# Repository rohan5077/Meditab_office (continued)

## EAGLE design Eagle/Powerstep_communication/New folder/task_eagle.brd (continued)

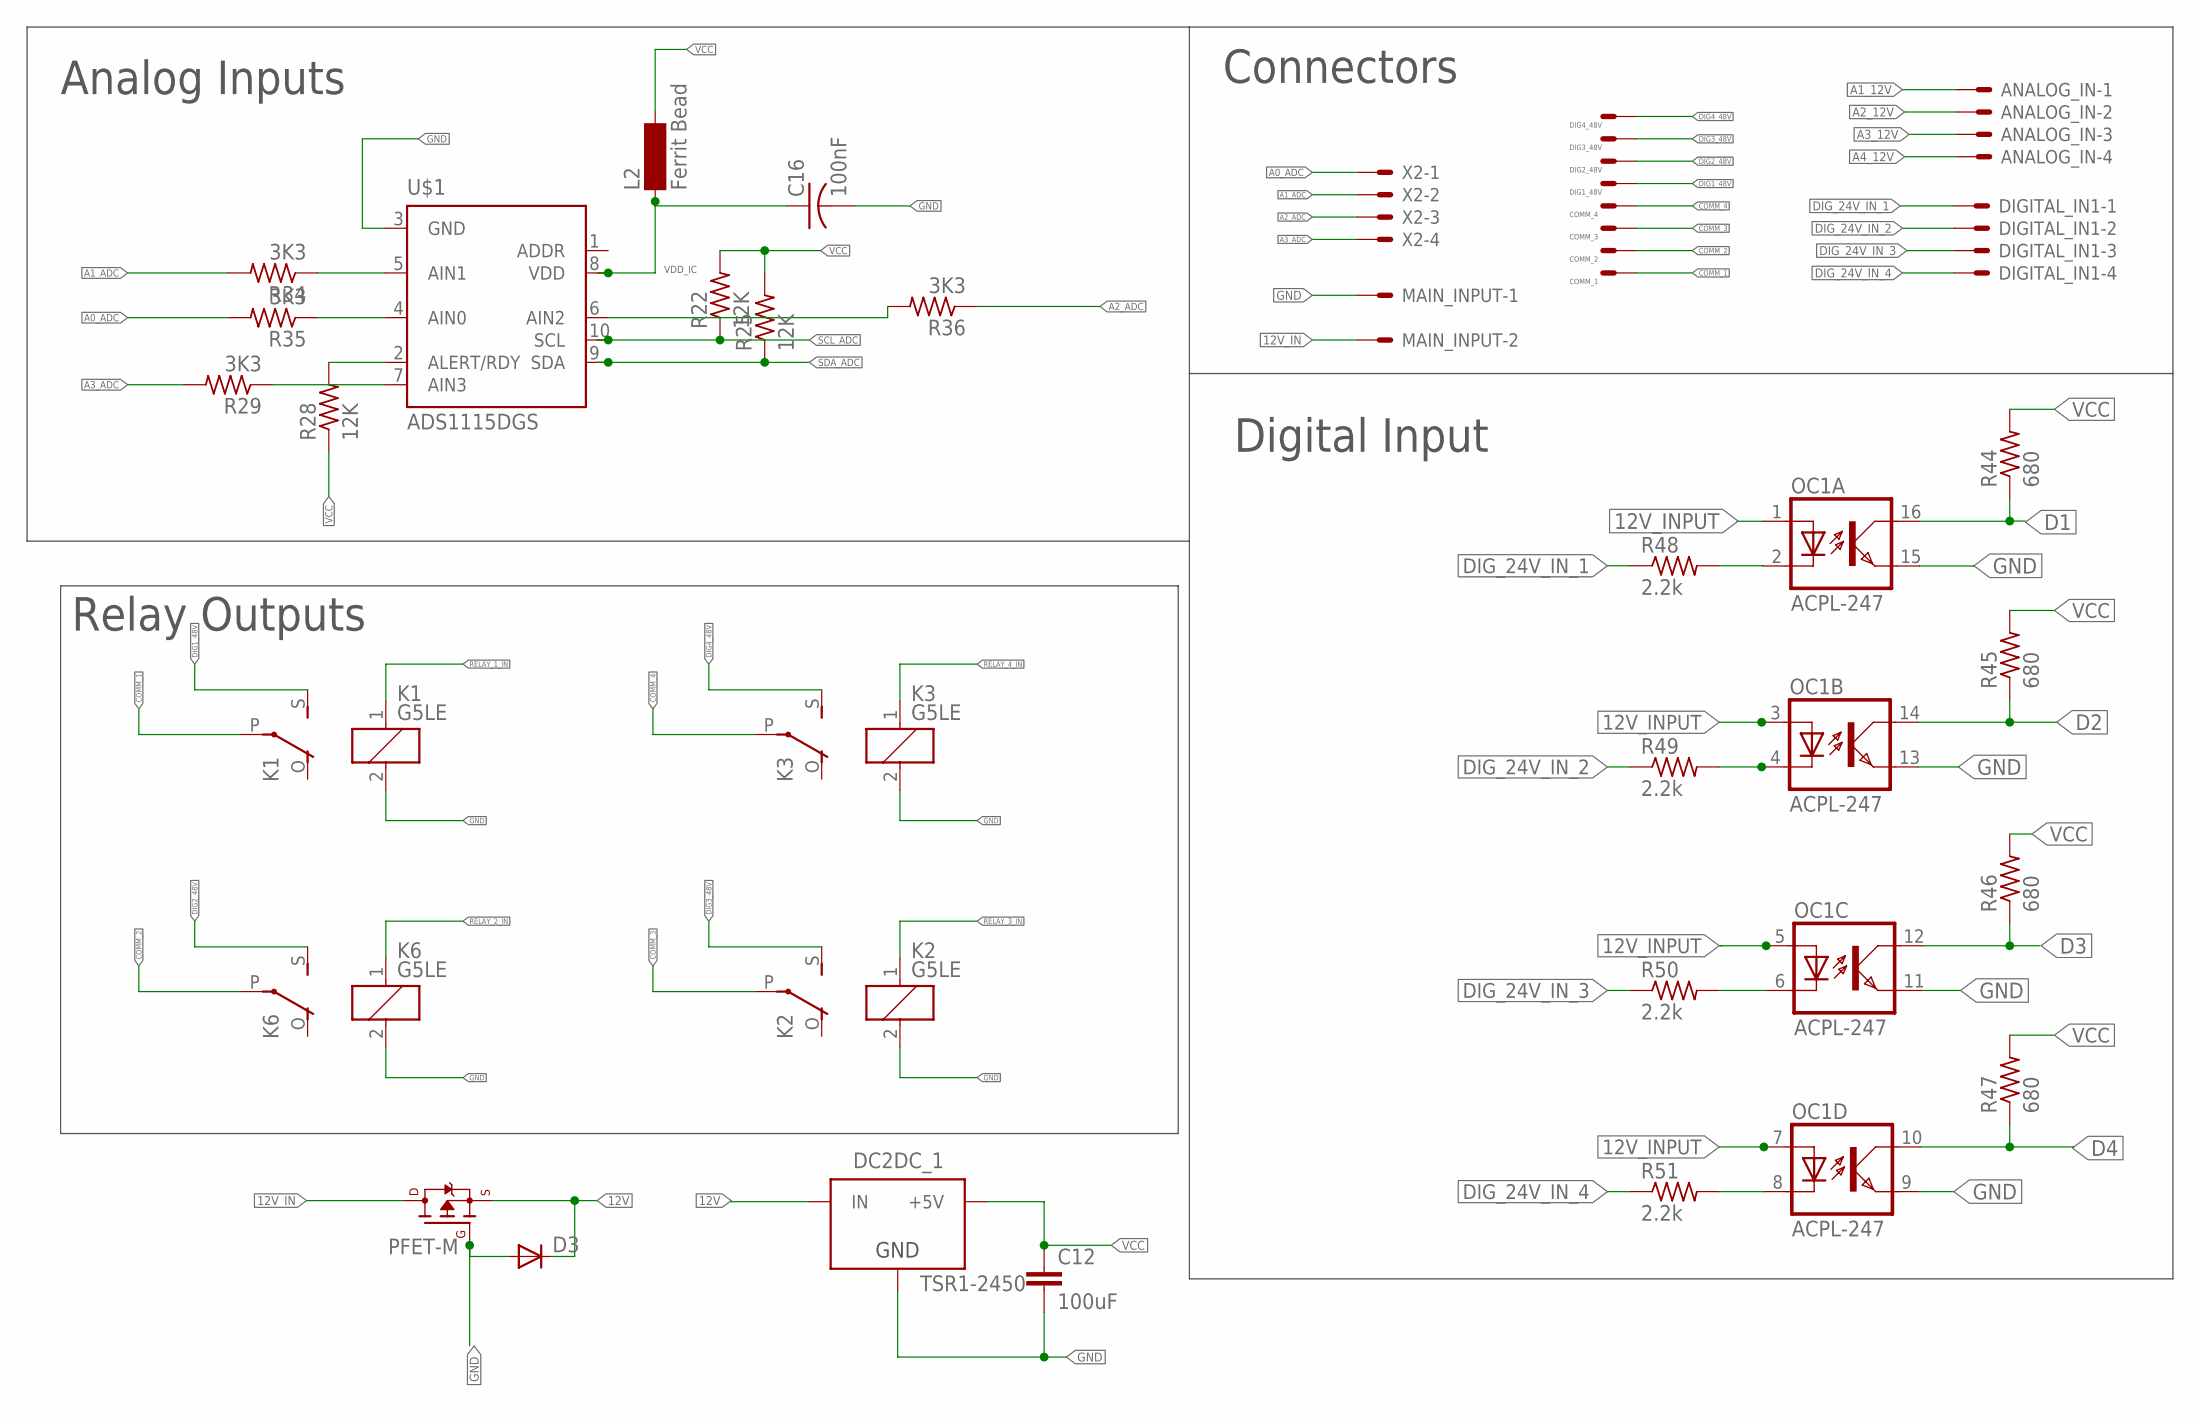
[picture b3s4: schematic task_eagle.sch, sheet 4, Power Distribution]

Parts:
ANALOG_IN: KK-156-4
C12: 100uF; C0603
C16: 100nF; C0603
D3: DIODE-MINIMELF; MINIMELF
DC2DC_1: TSR1-2450; TSR-1
DIGITAL_IN1: KK-156-4
K1, K2, K3, K6: G5LE
L2: Ferrit Bead; SM-1206
MAIN_INPUT: KK-156-2
OC1: ACPL-247; SOP16
PFET-M: FQP47P06NORMAL; FQP47P06-NORMAL
R22, R25, R28: 12K; R0603
R29, R34, R35, R36: 3K3; R0603
R44, R45, R46, R47: 680; R0603
R48, R49, R50, R51: 2.2k; R0603
U$1: ADS1115DGS; MSOP10
X2: KK-156-4
X3: KK-156-8

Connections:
12V: D3.C, DC2DC_1.1 (IN), PFET-M.3 (S)
12V_IN: MAIN_INPUT.2, PFET-M.2 (D)
12V_INPUT: OC1.1 (A), OC1.3 (A), OC1.5 (A), OC1.7 (A)
A0_ADC: R35.2, X2.1; also elsewhere on the board
A1_ADC: R34.2, X2.2; also elsewhere on the board
A2_ADC: R36.1, X2.3; also elsewhere on the board
A3_ADC: R29.2, X2.4; also elsewhere on the board
COMM_1: K1.P, X3.1
COMM_2: K6.P, X3.2
COMM_3: K2.P, X3.3
COMM_4: K3.P, X3.4
D1: OC1.16 (COL), R44.1; also elsewhere on the board
D2: OC1.14 (COL), R45.1; also elsewhere on the board
D3: OC1.12 (COL), R46.1; also elsewhere on the board
D4: OC1.10 (COL), R47.1; also elsewhere on the board
DIG1_48V: K1.S, X3.5
DIG2_48V: K6.S, X3.6
DIG3_48V: K2.S, X3.7
DIG4_48V: K3.S, X3.8
DIG_24V_IN_1: DIGITAL_IN1.1, R48.1
DIG_24V_IN_2: DIGITAL_IN1.2, R49.1
DIG_24V_IN_3: DIGITAL_IN1.3, R50.1
DIG_24V_IN_4: DIGITAL_IN1.4, R51.1
GND: C12.2, C16.2, D3.A, DC2DC_1.2 (GND), K1.2, K2.2, K3.2, K6.2, MAIN_INPUT.1, OC1.9 (EMIT), OC1.11 (EMIT), OC1.13 (EMIT), OC1.15 (EMIT), PFET-M.1 (G), U$1.3 (GND); also elsewhere on the board
unnamed 43: U$1.1 (ADDR); also elsewhere on the board
unnamed: R34.1, U$1.5 (AIN1)
unnamed: R35.1, U$1.4 (AIN0)
unnamed: R29.1, U$1.7 (AIN3)
unnamed: R28.2, U$1.2 (ALERT/RDY)
unnamed: R36.2, U$1.6 (AIN2)
unnamed: OC1.4 (C), R49.2
unnamed: OC1.8 (C), R51.2
unnamed: OC1.6 (C), R50.2
unnamed: OC1.2 (C), R48.2
RELAY_1_IN: K1.1; also elsewhere on the board
RELAY_2_IN: K6.1; also elsewhere on the board
RELAY_3_IN: K2.1; also elsewhere on the board
RELAY_4_IN: K3.1; also elsewhere on the board
SCL_ADC: R22.1, U$1.10 (SCL); also elsewhere on the board
SDA_ADC: R25.1, U$1.9 (SDA); also elsewhere on the board
VDD_IC: C16.1, L2.1, U$1.8 (VDD)

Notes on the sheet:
COMM_1
COMM_2
COMM_3
COMM_4
DIG1_48V
DIG2_48V
DIG3_48V
DIG4_48V
Analog Inputs
Relay Outputs
Connectors
Digital Input

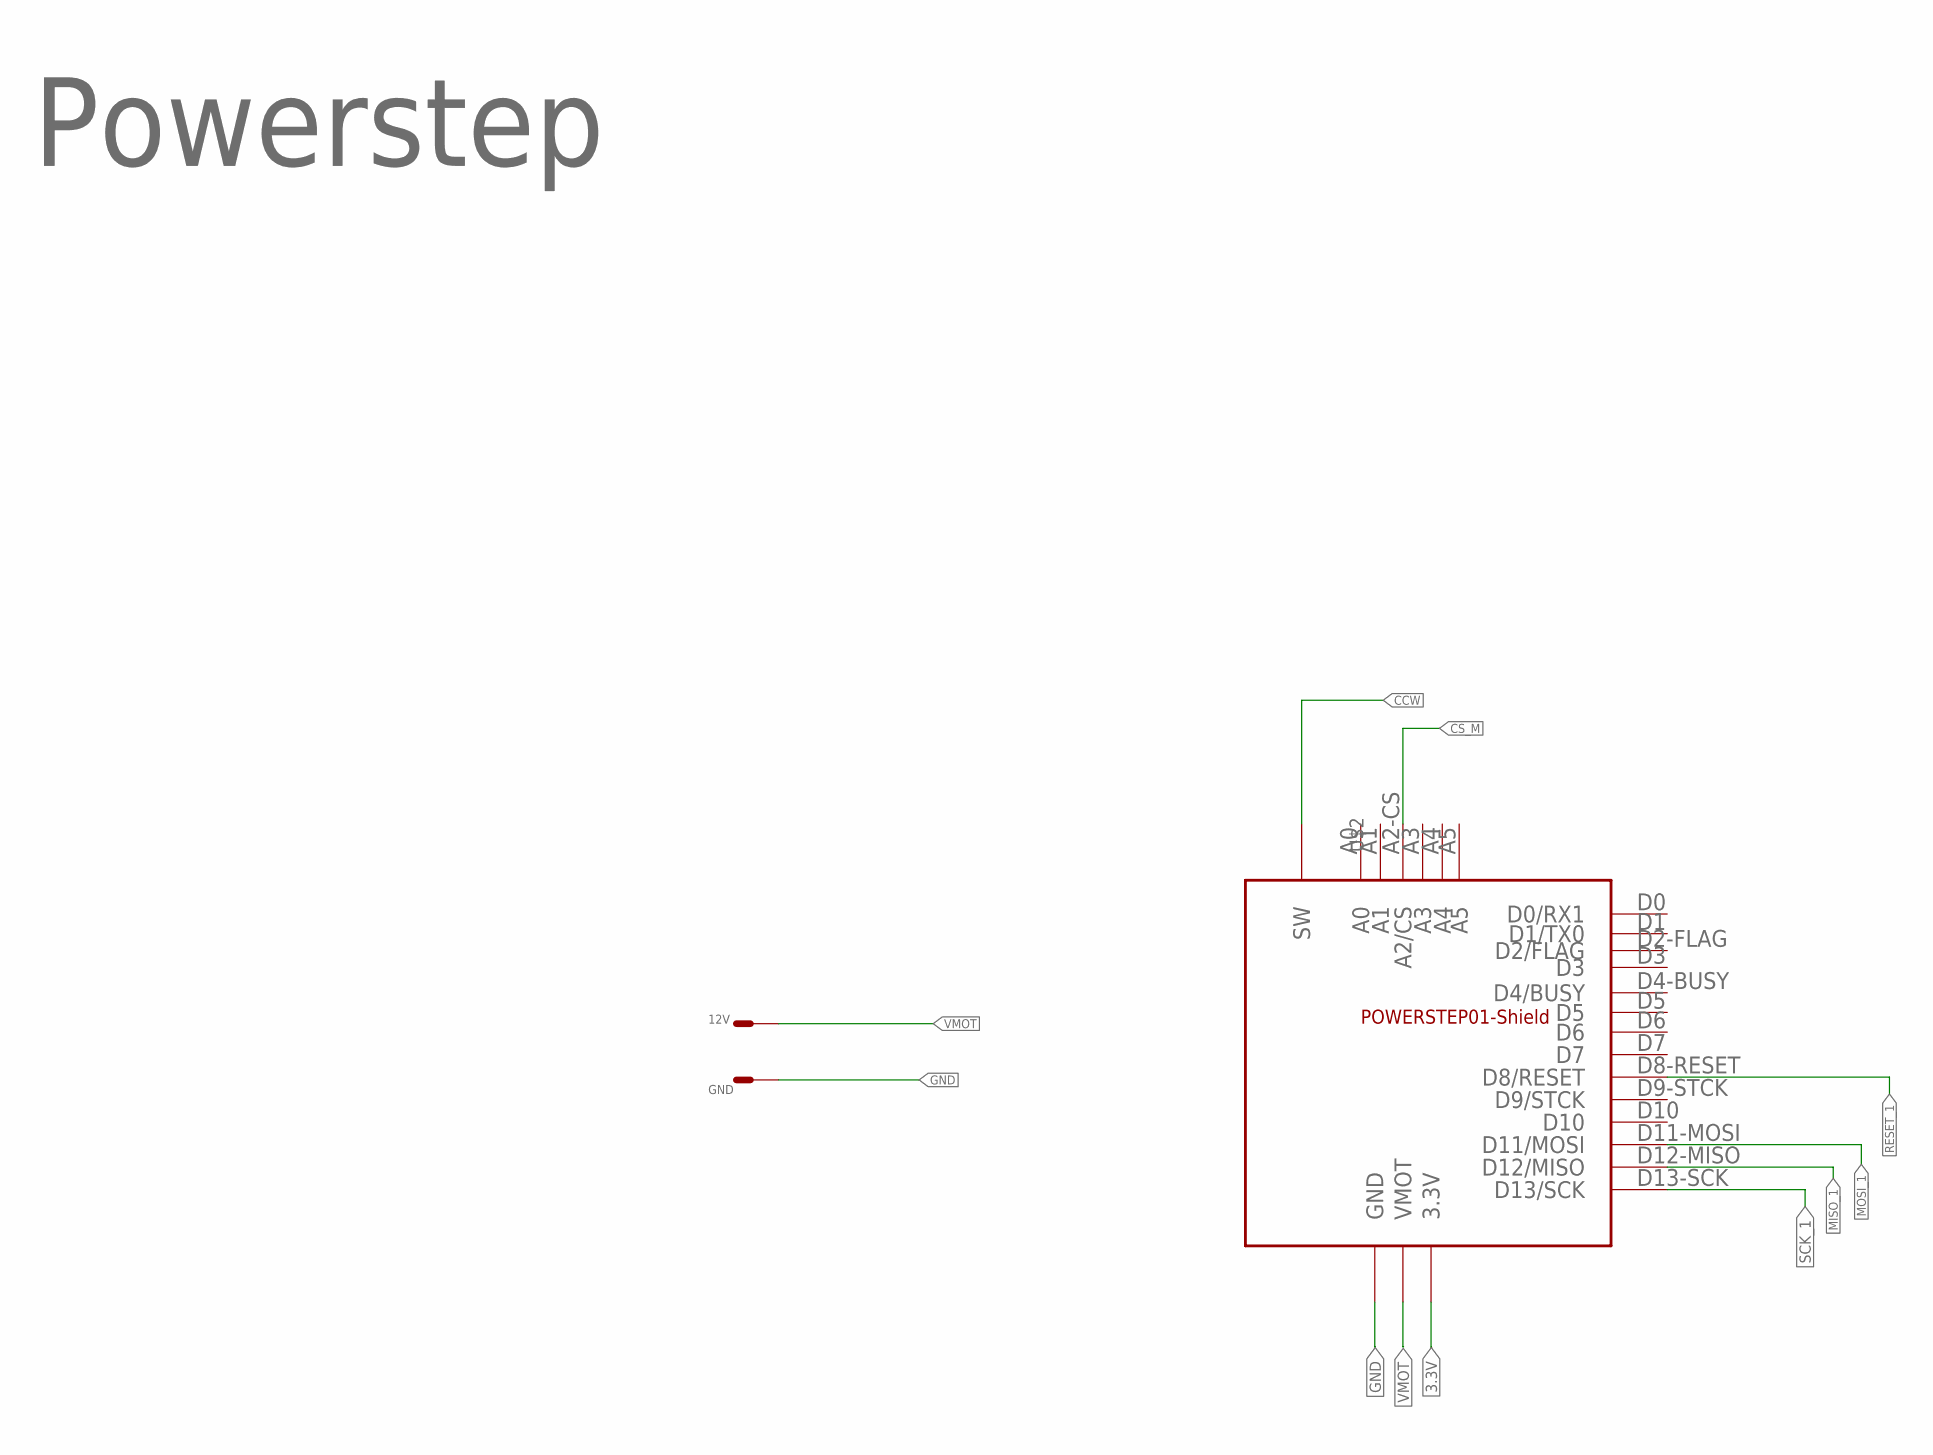
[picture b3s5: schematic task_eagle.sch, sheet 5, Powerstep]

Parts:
U$2: POWERSTEP01-SHIELD; POWERSTEP1
X1: KK-156-2

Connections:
3.3V: U$2.3.3V, U$2.IOREF (3.3V); also elsewhere on the board
CCW: U$2.SW; also elsewhere on the board
CS_M: U$2.A2-CS (A2/CS); also elsewhere on the board
GND: U$2.GND@0 (GND), U$2.GND@1 (GND), U$2.GND@2 (GND), U$2.GND@3 (GND), X1.1; also elsewhere on the board
MISO_1: U$2.D12-MISO (D12/MISO); also elsewhere on the board
MOSI_1: U$2.D11-MOSI (D11/MOSI); also elsewhere on the board
RESET_1: U$2.D8-RESET (D8/RESET); also elsewhere on the board
SCK_1: U$2.D13-SCK (D13/SCK); also elsewhere on the board
VMOT: U$2.VS+ (VMOT), X1.2

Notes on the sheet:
Powerstep
12V
GND

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
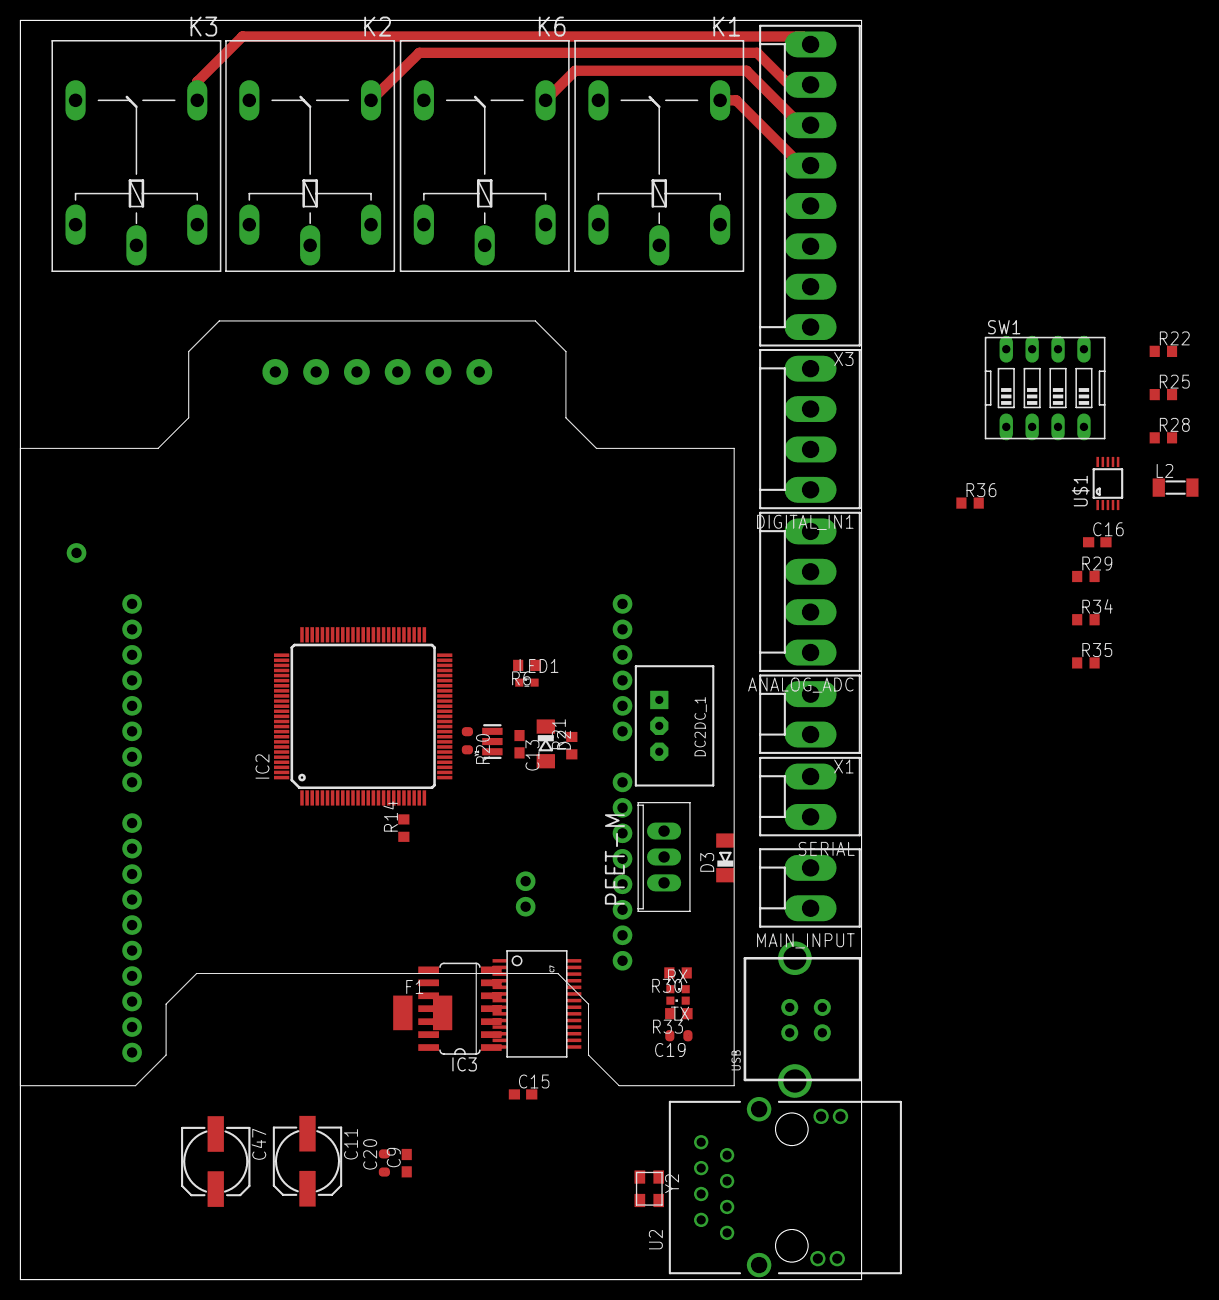
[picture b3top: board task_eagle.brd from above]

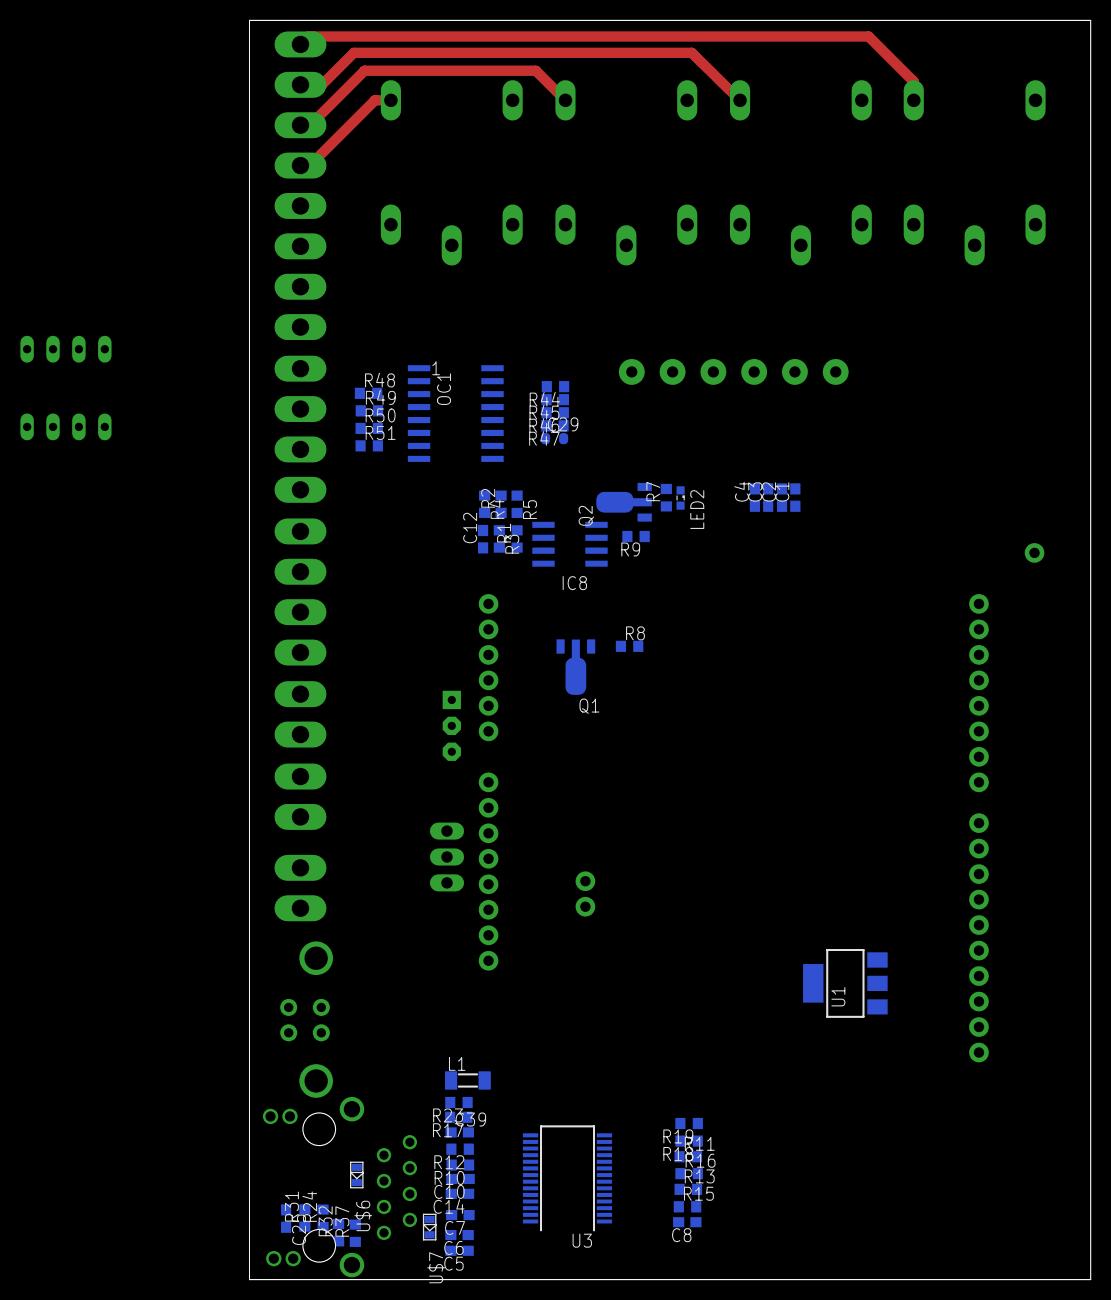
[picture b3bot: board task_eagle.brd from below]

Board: 2 copper layers, 82.5 x 123.5 mm, 104 parts (54 on the bottom side), 98 nets.

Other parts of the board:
ANALOG_ADC: KK-156-4
SW1: EDG-04

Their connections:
A0_ADC: ANALOG_ADC.1; also elsewhere on the board
A1_ADC: ANALOG_ADC.2; also elsewhere on the board
A2_ADC: ANALOG_ADC.3; also elsewhere on the board
A3_ADC: ANALOG_ADC.4; also elsewhere on the board
GND: SW1.8; also elsewhere on the board
unnamed 43: SW1.1, SW1.2, SW1.3, SW1.4; also elsewhere on the board
SCL_ADC: SW1.6; also elsewhere on the board
SDA_ADC: SW1.5; also elsewhere on the board

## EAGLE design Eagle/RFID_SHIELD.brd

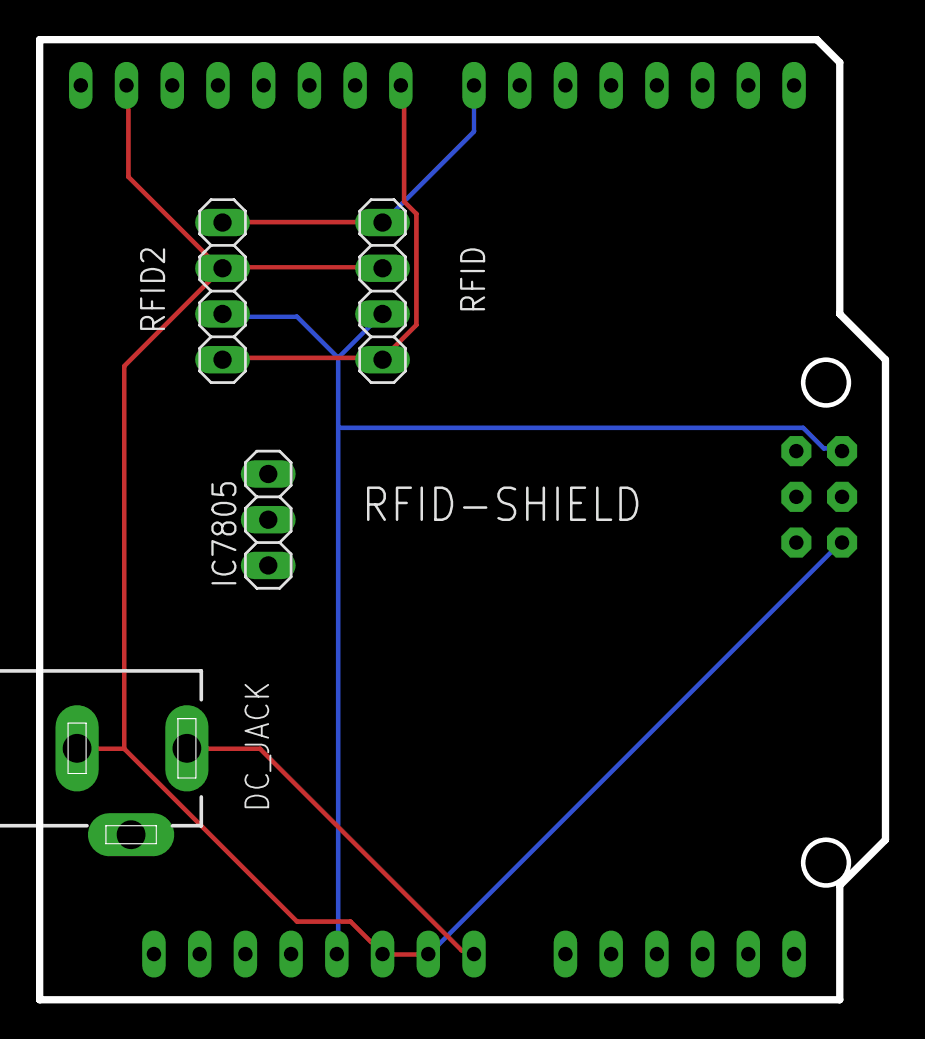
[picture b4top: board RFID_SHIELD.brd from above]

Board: 2 copper layers, 47.0 x 53.3 mm, 5 parts (0 on the bottom side), 5 nets.

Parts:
DC_JACK: DCJ0202
IC7805: 7805; 1X03
RFID, RFID2: 1X04
U$1: DRAGINO_SHIELD

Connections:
+5V: RFID.3, RFID2.3, U$1.5V, U$1.+5V
EN: RFID.1, RFID2.1, U$1.7
GND: DC_JACK.3, RFID.2, RFID2.2, U$1.GND, U$1.GND@1, U$1.GND@2, U$1.GND@3
TX: RFID.4, RFID2.4, U$1.8
VIN: DC_JACK.1, U$1.VIN
